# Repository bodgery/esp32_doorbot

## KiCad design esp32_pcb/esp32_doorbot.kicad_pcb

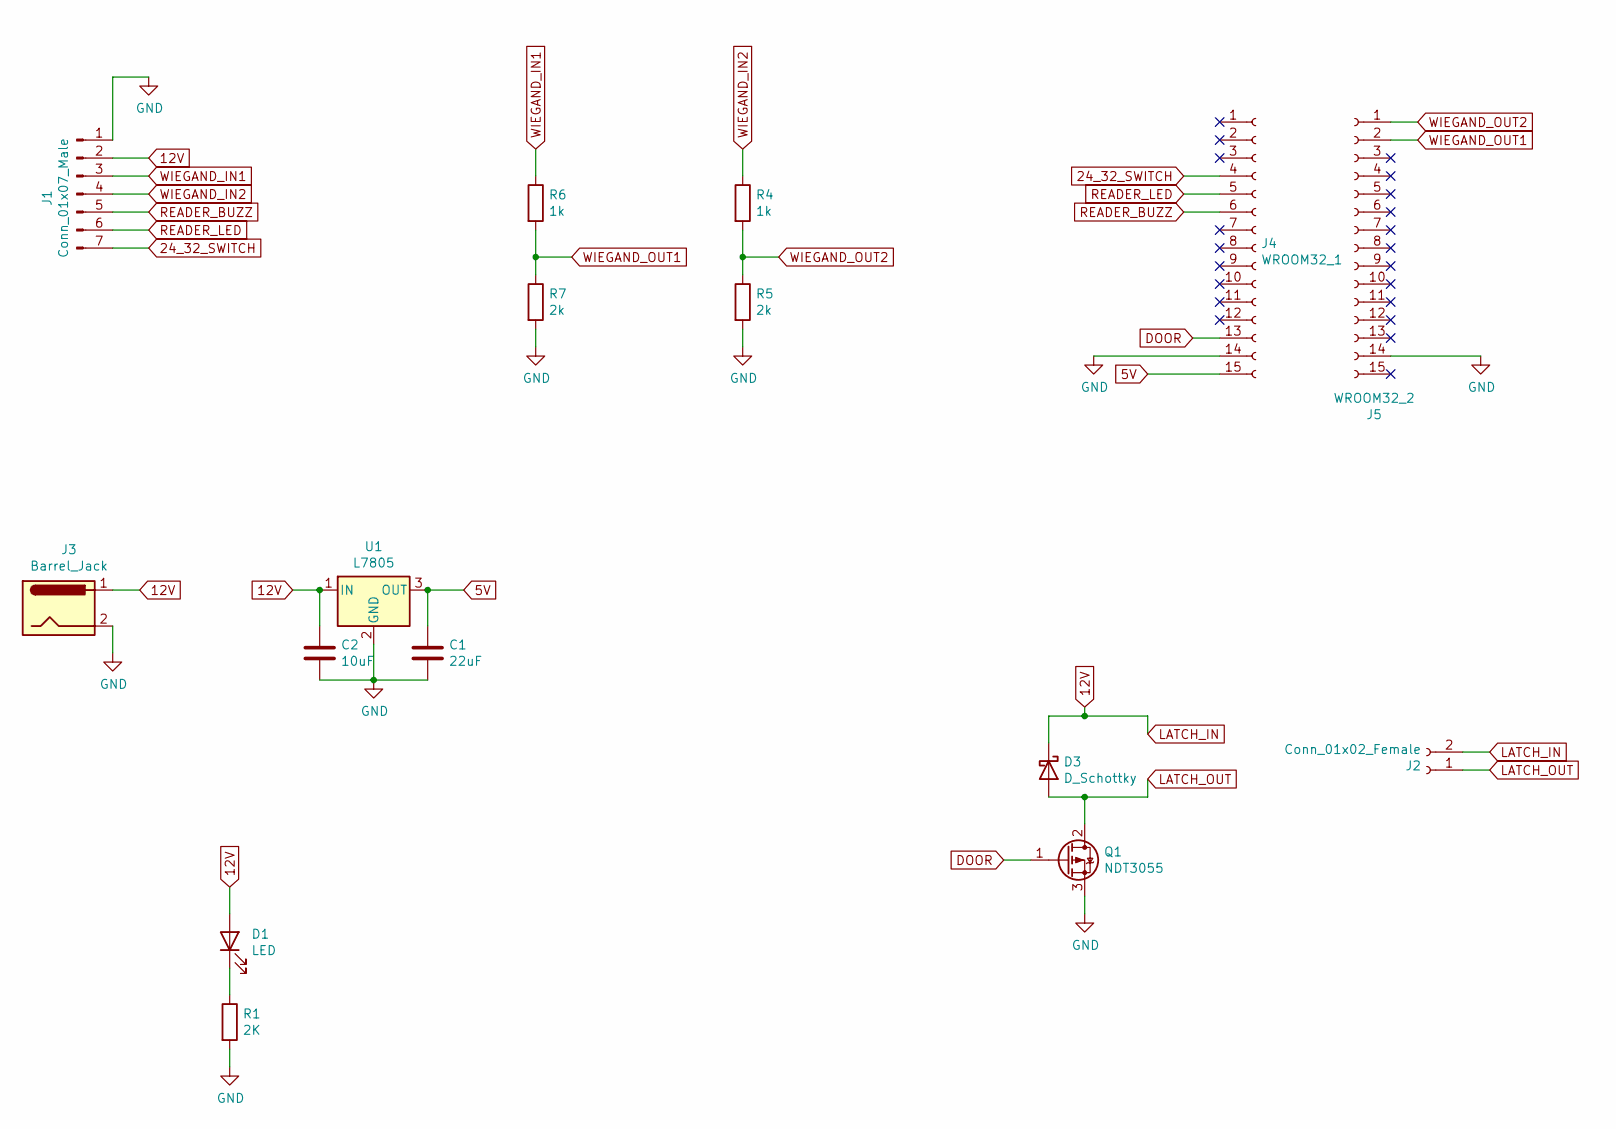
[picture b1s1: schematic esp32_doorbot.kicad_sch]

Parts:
C1: 22uF; C_1206; Digikey # 1276-1771-2-ND
C2: 10uF; C_1206; Digikey # 1276-6736-1-ND
D1: LED; LED-1206; Digikey # 1516-1073-2-N
D3: D_Schottky; SMD-1206_Pol; Digikey # 478-7805-2-ND
J1: Conn_01x07_Male; JST_ZH_B7B-ZR_1x07_P1.50mm_Vertical; Digikey # 455-1674-ND
J2: Conn_01x02_Female; TerminalBlock_Pheonix_MKDS1.5-2pol; Digikey # ED2561-ND
J3: Barrel_Jack; Tensility 54-00166; Digikey # 839-54-00166-ND
J4: WROOM32_1; Pin_Header_Straight_1x15
J5: WROOM32_2; Pin_Header_Straight_1x15
Q1: NDT3055; SOT-223; Digikey # NDT3055CT-ND
R1: 2K; R_1210; Digikey # P2.0KVTR-ND
R4, R6: 1k; R_1210; Digikey # RMCF1210FT1K00
R5, R7: 2k; R_1210; Digikey # P2.0KVTR-ND
U1: L7805; TO-220_Neutral123_Vertical; Digikey # 1470-VR10S05-ND

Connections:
5V: C1.1, J4.15, U1.3 (OUT)
12V: C2.1, D1.2 (A), D3.1 (K), J1.2, J2.2, J3.1, U1.1 (IN)
24_32_SWITCH: J1.7, J4.4
DOOR: J4.13, Q1.1 (G)
GND: C1.2, C2.2, J1.1, J3.2, J4.14, J5.14, Q1.3 (S), R1.2, R5.2, R7.2, U1.2 (GND)
LATCH_OUT: D3.2 (A), J2.1, Q1.2 (D)
unnamed: D1.1 (K), R1.1
READER_BUZZ: J1.5, J4.6
READER_LED: J1.6, J4.5
WIEGAND_IN1: J1.3, R6.1
WIEGAND_IN2: J1.4, R4.1
WIEGAND_OUT1: J5.2, R6.2, R7.1
WIEGAND_OUT2: J5.1, R4.2, R5.1

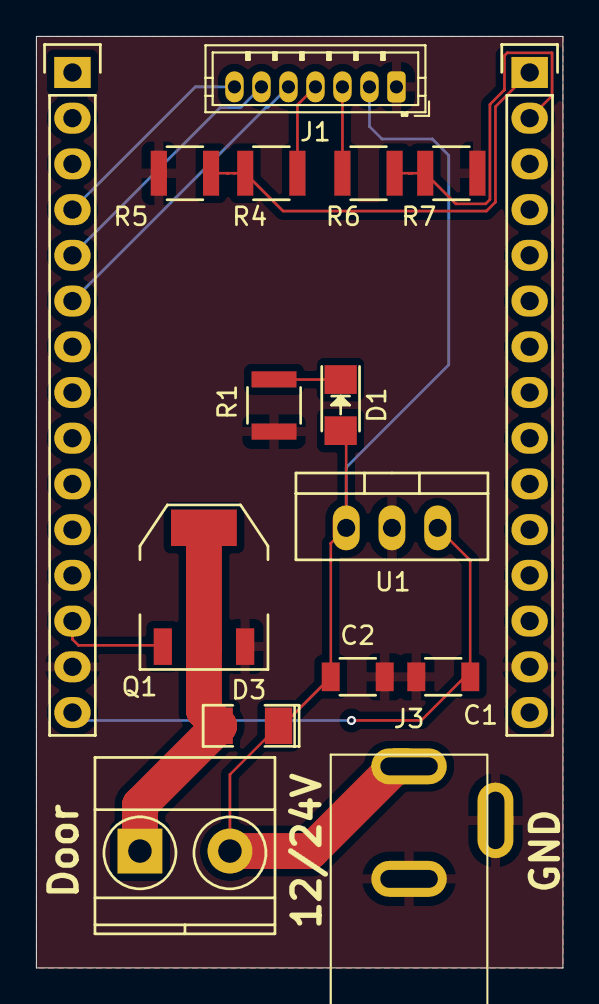
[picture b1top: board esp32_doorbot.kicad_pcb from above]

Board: 2 copper layers, 29.2 x 51.8 mm, 16 parts (0 on the bottom side), 13 nets.

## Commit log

2024-02-12 Remove tone generation
2024-03-04 Update SSL cert chain. Log gateway IP.
2024-06-05 Port over to platformio
2024-07-12 Revert "Port over to platformio"
    This reverts commit 211ea1fda4d62eb3cba9dac94291a7e6b76c643d.
2025-05-29 Update TLS cert. Initial support for reconnecting to wifi on disconnect.
2025-05-29 Use event-driven interface for WiFi disconnect/reconnect
2025-06-07 Reconnect to WiFi when it goes down
2025-07-25 Uhh, changes that got left behind. No, this isn't a good way to write config messages
2025-07-25 OTA updates implemented
2025-09-23 Update Lets Encrypt root certs
2025-09-26 Allow the output to be config'd normally high or normally low. Update the config file example with lots of extra possibilities.
2025-09-28 Convert power screw terminal into barrel jack. Convert back pin header to proper JST-ZH connector.
2025-09-28 old backup files
2025-11-13 Gerber/drill files for PCBWay

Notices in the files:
esp32_pcb/esp32_doorbot.kicad_pcb:
Copyright © 2021
